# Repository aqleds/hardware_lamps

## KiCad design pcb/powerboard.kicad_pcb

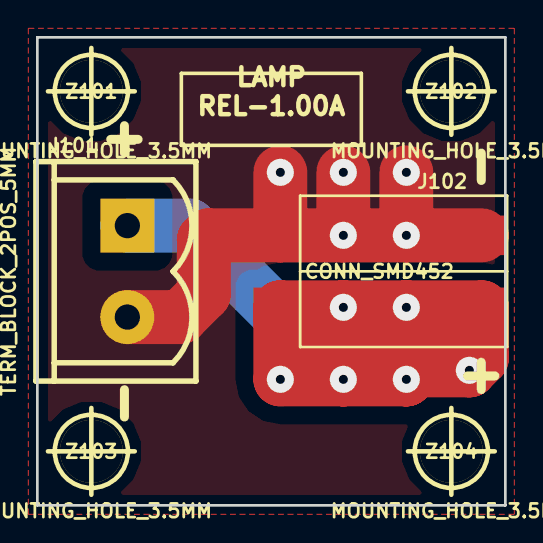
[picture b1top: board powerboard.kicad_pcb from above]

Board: 2 copper layers, 26.0 x 26.0 mm, 7 parts (0 on the bottom side), 2 nets.

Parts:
J101: TERM_BLOCK_2POS_5MM; CONN_PHOENIX_2,5/2-G-5,08
J102: CONN_SMD452; SMD452
Z101, Z102, Z103, Z104: MOUNTING_HOLE_3.5MM; HOLE_PLATED_3.5MM
Z105: AQLEDS_LOGO

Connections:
+12V: J101.1, J102.1, J102.3
GND: J101.2, J102.2, J102.4

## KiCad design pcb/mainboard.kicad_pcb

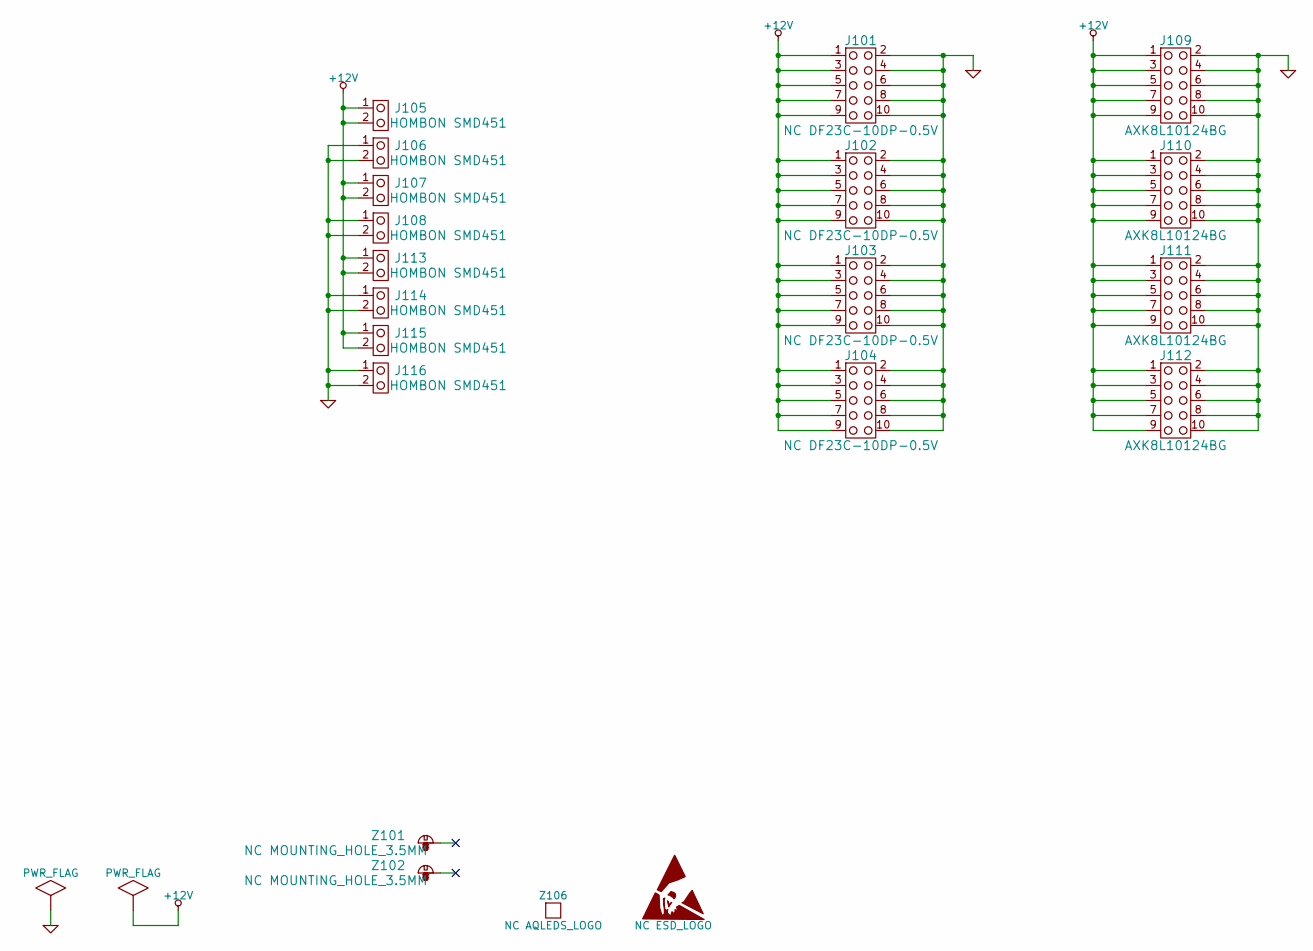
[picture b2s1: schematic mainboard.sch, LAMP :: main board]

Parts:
J101, J102, J103, J104: HIROSE_DF23C-10DP-0.5V
J105, J106, J107, J108, J113, J114, J115, J116: CONN_SMD451; SMD451
J109, J110, J111, J112: PANASONIC_AXK8L10124BG
Z101, Z102: MOUNTING_HOLE_3.5MM; HOLE_PLATED_3.5MM
Z106: AQLEDS_LOGO
Z107: ESD_LOGO

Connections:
+12V: J101.1, J101.3, J101.5, J101.7, J101.9, J102.1, J102.3, J102.5, J102.7, J102.9, J103.1, J103.3, J103.5, J103.7, J103.9, J104.1, J104.3, J104.5, J104.7, J104.9, J105.1, J105.2, J107.1, J107.2, J109.1, J109.3, J109.5, J109.7, J109.9, J110.1, J110.3, J110.5, J110.7, J110.9, J111.1, J111.3, J111.5, J111.7, J111.9, J112.1, J112.3, J112.5, J112.7, J112.9, J113.1, J113.2, J115.1, J115.2
GND: J101.2, J101.4, J101.6, J101.8, J101.10, J102.2, J102.4, J102.6, J102.8, J102.10, J103.2, J103.4, J103.6, J103.8, J103.10, J104.2, J104.4, J104.6, J104.8, J104.10, J106.1, J106.2, J108.1, J108.2, J109.2, J109.4, J109.6, J109.8, J109.10, J110.2, J110.4, J110.6, J110.8, J110.10, J111.2, J111.4, J111.6, J111.8, J111.10, J112.2, J112.4, J112.6, J112.8, J112.10, J114.1, J114.2, J116.1, J116.2

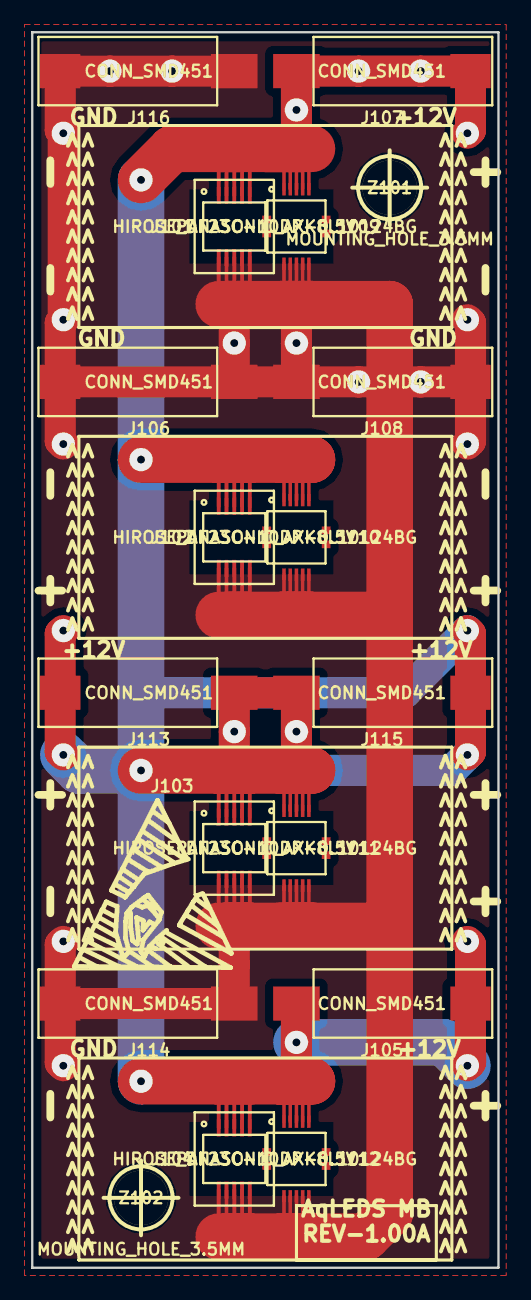
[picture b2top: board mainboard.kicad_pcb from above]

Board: 2 copper layers, 30.0 x 79.5 mm, 20 parts (0 on the bottom side), 2 nets.

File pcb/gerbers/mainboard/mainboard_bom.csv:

ref;Value;DescriptionJ101;NC DF23C-10DP-0.5V;Hirose - DF23C-10DP-0.5VJ102;NC DF23C-10DP-0.5V;Hirose - DF23C-10DP-0.5VJ103;NC DF23C-10DP-0.5V;Hirose - DF23C-10DP-0.5VJ104;NC DF23C-10DP-0.5V;Hirose - DF23C-10DP-0.5VJ105;HOMBON SMD451;Connector 1 SIL SMD SMD451J106;HOMBON SMD451;Connector 1 SIL SMD SMD451J107;HOMBON SMD451;Connector 1 SIL SMD SMD451J108;HOMBON SMD451;Connector 1 SIL SMD SMD451J109;AXK8L10124BG;Panasonic - AXK8L10124BGJ110;AXK8L10124BG;Panasonic - AXK8L10124BGJ111;AXK8L10124BG;Panasonic - AXK8L10124BGJ112;AXK8L10124BG;Panasonic - AXK8L10124BGJ113;HOMBON SMD451;Connector 1 SIL SMD SMD451J114;HOMBON SMD451;Connector 1 SIL SMD SMD451J115;HOMBON SMD451;Connector 1 SIL SMD SMD451J116;HOMBON SMD451;Connector 1 SIL SMD SMD451Z101;NC MOUNTING_HOLE_3.5MM;Mounting Hole 3.5MM opening platedZ102;NC MOUNTING_HOLE_3.5MM;Mounting Hole 3.5MM opening platedZ106;NC AQLEDS_LOGO;AQLEDS Aqua LEDs LogoZ107;NC ESD_LOGO;ESD Logo Symbol

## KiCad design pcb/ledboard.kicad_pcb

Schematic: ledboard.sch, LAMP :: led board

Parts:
D101, D104: HL-AF-5060H343W-3-S1-T1; LED-SMD-6
D102, D105: HTLB4A-46; LED-SMD-6
D103, D106: HTLB4A-48; LED-SMD-6
J101: HIROSE_DF23C-10DS-0.5V
J102: PANASONIC_AXK7L10223G
R101, R102, R107, R108: 0R_0603; R_0603; tolerance 1%
R103, R104, R105, R106: NCR_0603; R_0603
Z101: AQLEDS_LOGO

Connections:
+12V: J101.1, J101.3, J101.5, J101.7, J101.9, J102.1, J102.3, J102.5, J102.7, J102.9, R101.1, R102.1, R103.1, R104.1
/LED_1: D101.4, D101.5, D101.6, R101.2, R105.2
/LED_2: D104.4, D104.5, D104.6, R102.2, R106.2
/LED_3: D103.1, D103.2, D103.3, R103.2, R107.2
/LED_4: D106.1, D106.2, D106.3, R104.2, R108.2
GND: J101.2, J101.4, J101.6, J101.8, J101.10, J102.2, J102.4, J102.6, J102.8, J102.10, R105.1, R106.1, R107.1, R108.1
unnamed: D101.1, D101.2, D101.3, D102.4, D102.5, D102.6
unnamed: D105.1, D105.2, D105.3, D106.4, D106.5, D106.6
unnamed: D102.1, D102.2, D102.3, D103.4, D103.5, D103.6
unnamed: D104.1, D104.2, D104.3, D105.4, D105.5, D105.6

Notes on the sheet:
Colour Lum (mcd - A) Lum (adj - A) V (V) R (ohm) I (A - 90% lum) V (V - 90% lum) R (ohm - 90% lum) White 6000 - 0.06 600 - 0.0075-0.01 2.75 250-187.5 0.055 3.1 24.5 Blue 530 - 0.06 530 - 0.06 3.3 17.5 - - - Red 1300 - 0.06 650 - 0.035 2.0 50 0.055 2.1 51.8

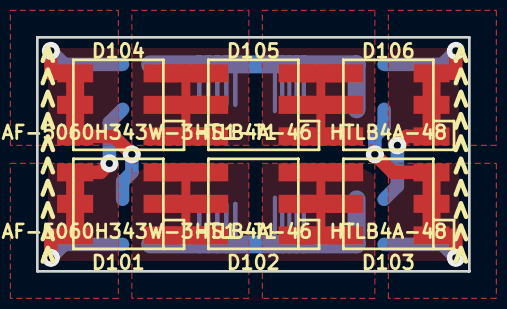
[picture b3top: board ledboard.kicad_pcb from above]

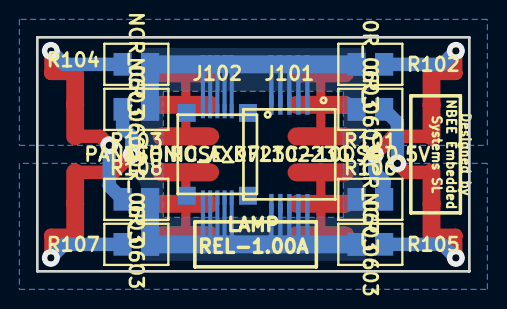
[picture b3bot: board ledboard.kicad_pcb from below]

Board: 2 copper layers, 24.0 x 13.0 mm, 17 parts (11 on the bottom side), 10 nets.

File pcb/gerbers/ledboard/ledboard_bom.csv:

ref;Field2;Field4D101;5060 LED;D102;5060 LED;D103;5060 LED;D104;5060 LED;D105;5060 LED;D106;5060 LED;J101;NC DF23C-10DS-0.5V;J102;AXK7L10223G;SMD ConnectorR101;100 Ohm;0603 100 ohm resR102;100 Ohm;0603 100 ohm resR103;NCR;NOT_ASSEMBLE - NOT_ASSEMBLER104;NCR;NOT_ASSEMBLE - NOT_ASSEMBLER105;NCR;NOT_ASSEMBLE - NOT_ASSEMBLER106;NCR;NOT_ASSEMBLE - NOT_ASSEMBLER107;0R 0603;Bourns - CR0603-J/-000ELFR108;0R 0603;Bourns - CR0603-J/-000ELF
